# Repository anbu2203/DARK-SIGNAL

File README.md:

## Dark Signal: The Batman Blinky Board
Building this project was a huge milestone for me. I wanted to move beyond a basic "LED on a breadboard" and create something that actually looked like it belonged in Gotham. Using the Hack Club guide was a game-changer; it turned the intimidating world of PCB design into a fun, step-by-step puzzle that I actually enjoyed solving.
## PCB IMAGES

It showcases the 3mm Red LEDs following the curves of the wings and the NE555P/4017 chips acting as the central "engine."
The Potentiometer (RV1) is prominently placed, allowing the user to manually dial in the speed of the chasing lights.

This view highlights the clean copper paths that carry signals between the chips and the LEDs. It shows the tidy Through-Hole pads where the components will be permanently joined to the board, giving it a professional, high-quality finish.

The board outline is a custom DXF import on the Edge.Cuts layer, creating the bat-wing shape. This view shows the "rat's nest" turned into organized traces on both the Top (Red) and Bottom (Blue) copper layers to avoid collisions.The LEDs are balanced across both wings to ensure the light sequence looks uniform when the board is powered on.
## schematic 

The NE555P is wired in Astable Mode, creating a continuous pulse that acts as the heartbeat for the lights. You can see Pin 3 (OUT) of the 555 timer feeding directly into Pin 14 (CLK) of the 4017 counter to drive the animation.A 470 Ω resistor (R1) is placed at the end of the LED chain to limit current and prevent the LEDs from burning out.
## thanks
Huge thanks to the Hack Club community for the guidance and inspiration. This project turned a bunch of random components into a pulsing Bat-signal, and I couldn't be more proud of the final "ship."
## bill of materials (BOM)
- 1uF capacitor x 1
- 0.01uF capacitor x 1
- led x 10
- 1k resistor x 1
- 470 ohm resistor x 1
- 50K resistor x 1
- testpoint connector x 3
- NEE555P IC x 1
- 4017 IC x 1
- tOTAL Estimated Build Cost=$15.15 - $20.15

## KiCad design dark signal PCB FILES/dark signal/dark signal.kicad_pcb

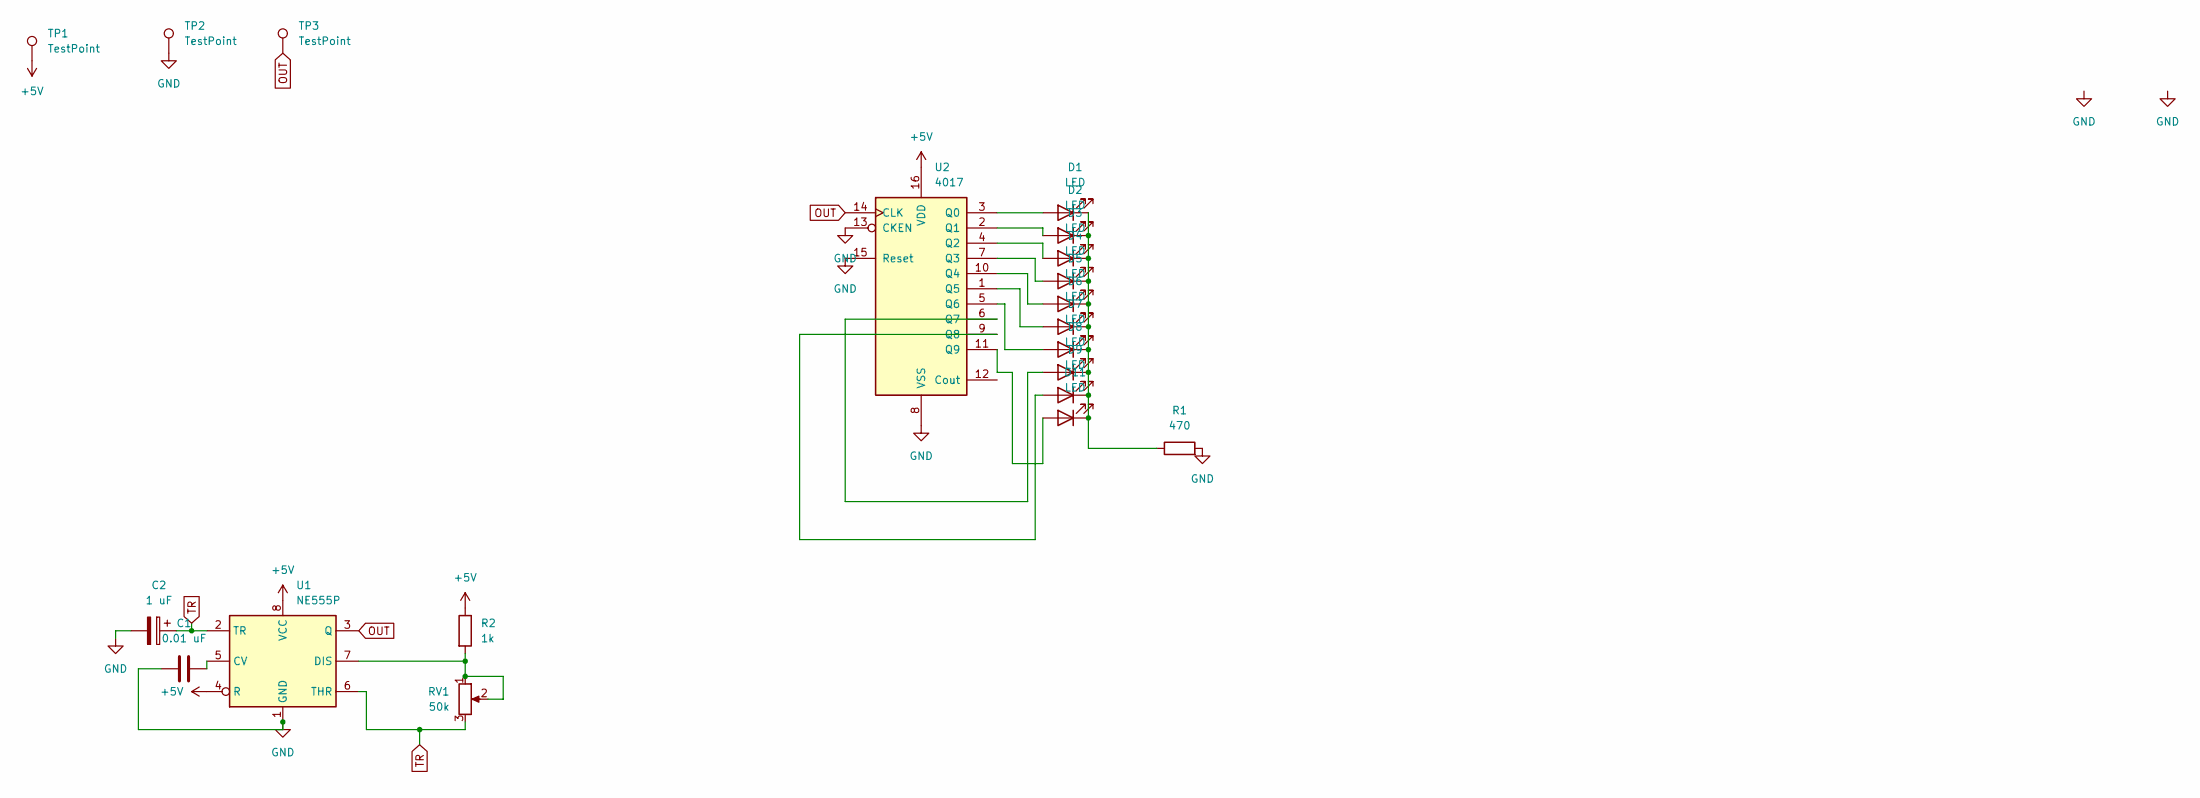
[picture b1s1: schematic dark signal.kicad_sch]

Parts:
C1: 0.01 uF; CP_Radial_D5.0mm_P2.00mm
C2: 1 uF; CP_Radial_D5.0mm_P2.00mm
D1, D2, D3, D4, D5, D6, D7, D8, D9, D11: LED; LED_D3.0mm
R1: 470; R_Axial_DIN0207_L6.3mm_D2.5mm_P7.62mm_Horizontal
R2: 1k; R_Axial_DIN0207_L6.3mm_D2.5mm_P7.62mm_Horizontal
RV1: 50k; Potentiometer_Bourns_PTV09A-1_Single_Vertical
TP1, TP2, TP3: TestPoint; PinSocket_1x01_P2.54mm_Vertical
U1: NE555P; DIP-8_W7.62mm
U2: 4017; N16

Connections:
+5V: R2.1, TP1.1, U1.4 (R), U1.8 (VCC), U2.16 (VDD)
GND: C1.1, C2.2, R1.2, TP2.1, U1.1 (GND), U2.8 (VSS), U2.13 (CKEN), U2.15 (Reset)
unnamed: D1.2 (A), U2.3 (Q0)
unnamed: D1.1 (K), D2.1 (K), D3.1 (K), D4.1 (K), D5.1 (K), D6.1 (K), D7.1 (K), D8.1 (K), D9.1 (K), D11.1 (K), R1.1
unnamed: D2.2 (A), U2.2 (Q1)
unnamed: D3.2 (A), U2.4 (Q2)
unnamed: D4.2 (A), U2.7 (Q3)
unnamed: D5.2 (A), U2.10 (Q4)
unnamed: D6.2 (A), U2.1 (Q5)
unnamed: D7.2 (A), U2.5 (Q6)
unnamed: D8.2 (A), U2.6 (Q7)
unnamed: D9.2 (A), U2.9 (Q8)
unnamed: D11.2 (A), U2.11 (Q9)
unnamed: C1.2, U1.5 (CV)
unnamed: R2.2, RV1.1, RV1.2, U1.7 (DIS)
OUT: TP3.1, U1.3 (Q), U2.14 (CLK)
TR: C2.1, RV1.3, U1.2 (TR), U1.6 (THR)

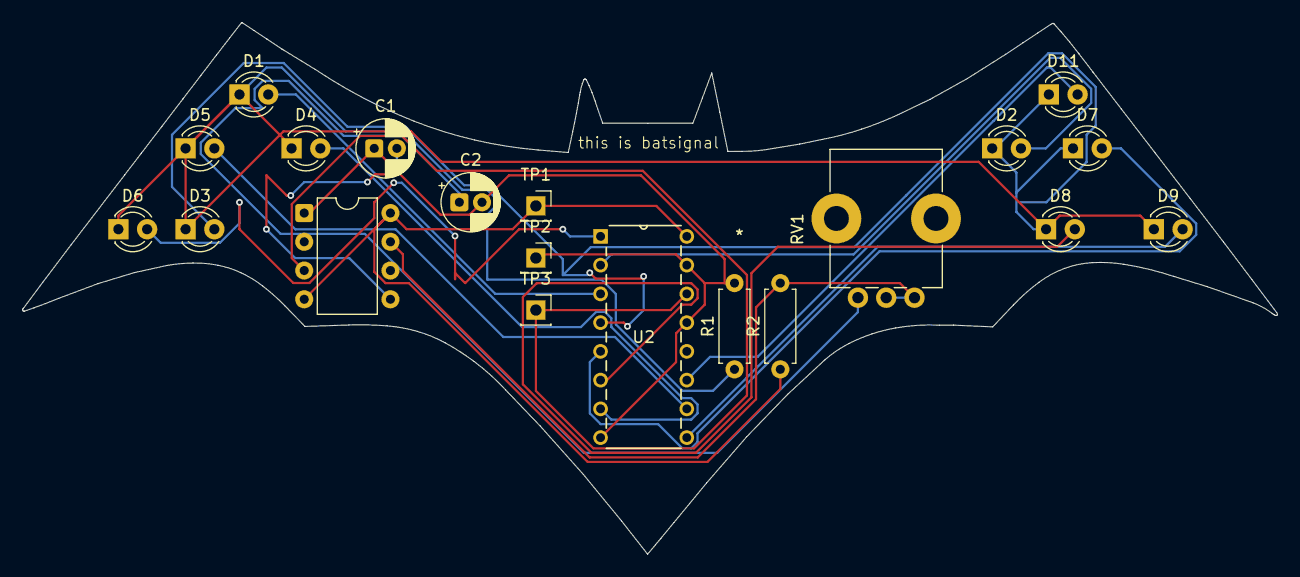
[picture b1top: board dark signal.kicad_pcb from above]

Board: 2 copper layers, 110.9 x 47.0 mm, 20 parts (0 on the bottom side), 17 nets.

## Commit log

2026-01-05 Fix image links in README.md
